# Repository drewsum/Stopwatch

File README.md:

# Stopwatch
Hardware stopwatch, no code or microcontroller. 

"Display Enable" pushbutton toggles the seven segment LED display on and off
"Count Reset" pushbutton resets the counted time back to 00:00:00
"Count Enable" pushbutton starts and stops the stopwatch

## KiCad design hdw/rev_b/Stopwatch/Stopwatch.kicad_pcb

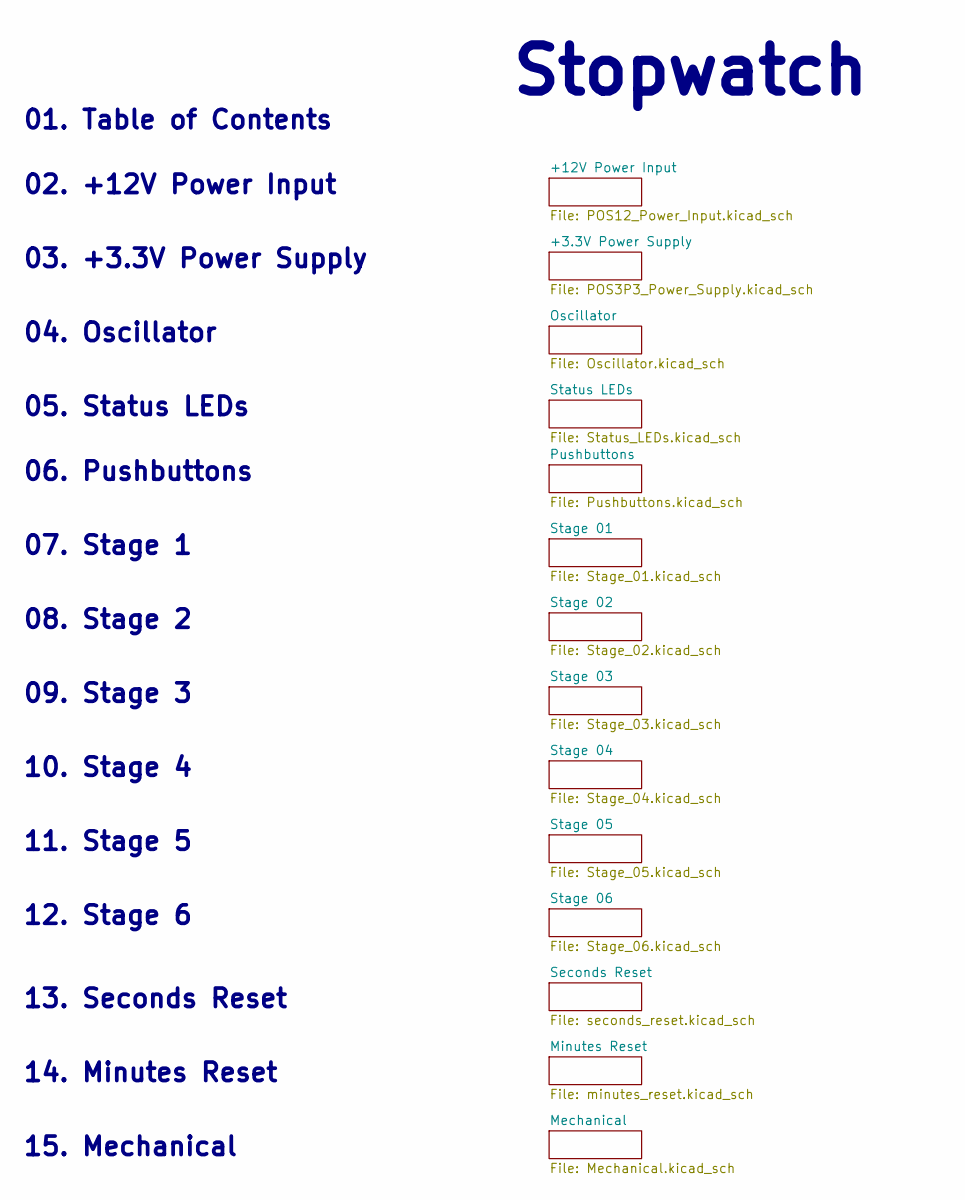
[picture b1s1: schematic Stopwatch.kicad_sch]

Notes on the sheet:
12. Stage 6
09. Stage 3
05. Status LEDs
10. Stage 4
15. Mechanical
Stopwatch
03. +3.3V Power Supply
01. Table of Contents
14. Minutes Reset
08. Stage 2
06. Pushbuttons
02. +12V Power Input
07. Stage 1
11. Stage 5
13. Seconds Reset
04. Oscillator

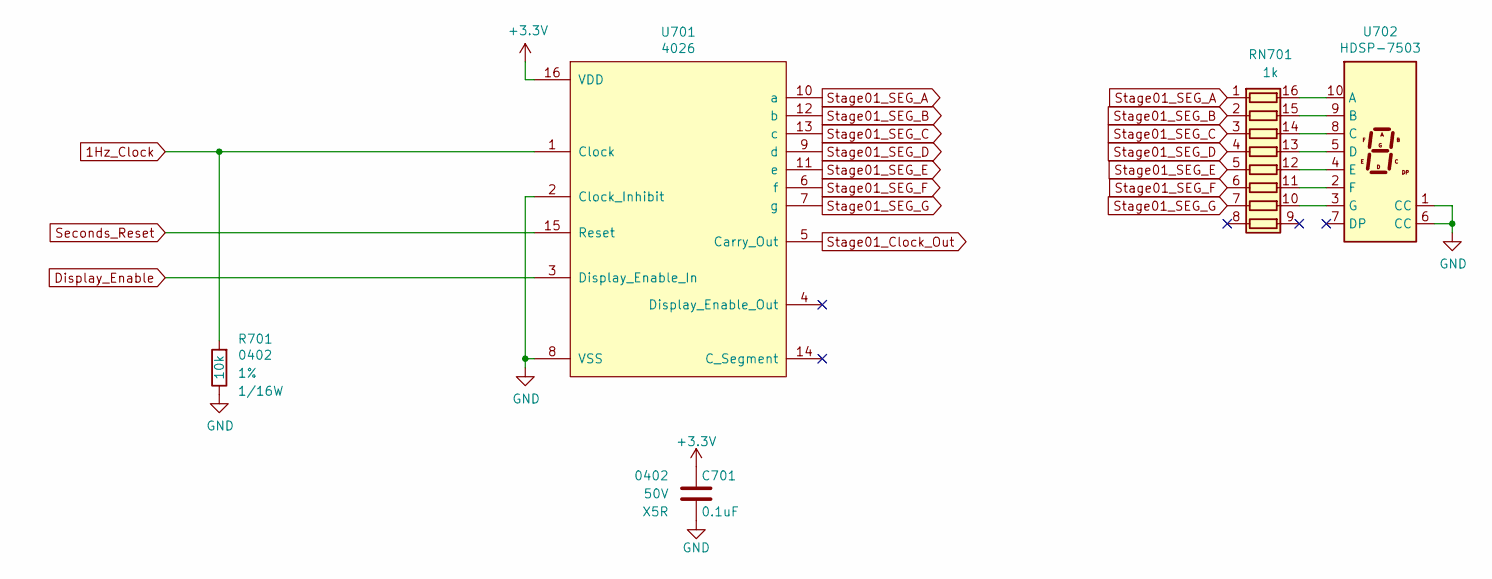
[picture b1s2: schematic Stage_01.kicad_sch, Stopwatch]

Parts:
C701: 0.1uF; C_0402; Voltage 50V; Digi-Key PN 490-10697-1-ND
R701: 10k; R_0402; Tolerance 1%; Digi-Key PN RMCF0402FT10K0CT-ND
RN701: 1k; R_Cat16-8; Digi-Key PN CAT16-102J8LFCT-ND
U701: 4026; TSSOP-16_4.4x5mm_Pitch0.65mm; Digi-Key PN 296-32878-5-ND
U702: HDSP-7503; HDSP-A151; Digi-Key PN 516-1203-5-ND

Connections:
1Hz_Clock: R701.1, U701.1 (Clock); also elsewhere on the board
+3.3V: C701.1, U701.16 (VDD); also elsewhere on the board
Display_Enable: U701.3 (Display_Enable_In); also elsewhere on the board
GND: C701.2, R701.2, U701.2 (Clock_Inhibit), U701.8 (VSS), U702.1 (CC), U702.6 (CC); also elsewhere on the board
unnamed: RN701.16 (R1.2), U702.10 (A)
unnamed: RN701.15 (R2.2), U702.9 (B)
unnamed: RN701.14 (R3.2), U702.8 (C)
unnamed: RN701.13 (R4.2), U702.5 (D)
unnamed: RN701.12 (R5.2), U702.4 (E)
unnamed: RN701.11 (R6.2), U702.2 (F)
unnamed: RN701.10 (R7.2), U702.3 (G)
Seconds_Reset: U701.15 (Reset); also elsewhere on the board
Stage01_Clock_Out: U701.5 (Carry_Out); also elsewhere on the board
Stage01_SEG_A: RN701.1 (R1.1), U701.10 (a)
Stage01_SEG_B: RN701.2 (R2.1), U701.12 (b)
Stage01_SEG_C: RN701.3 (R3.1), U701.13 (c)
Stage01_SEG_D: RN701.4 (R4.1), U701.9 (d)
Stage01_SEG_E: RN701.5 (R5.1), U701.11 (e)
Stage01_SEG_F: RN701.6 (R6.1), U701.6 (f)
Stage01_SEG_G: RN701.7 (R7.1), U701.7 (g)

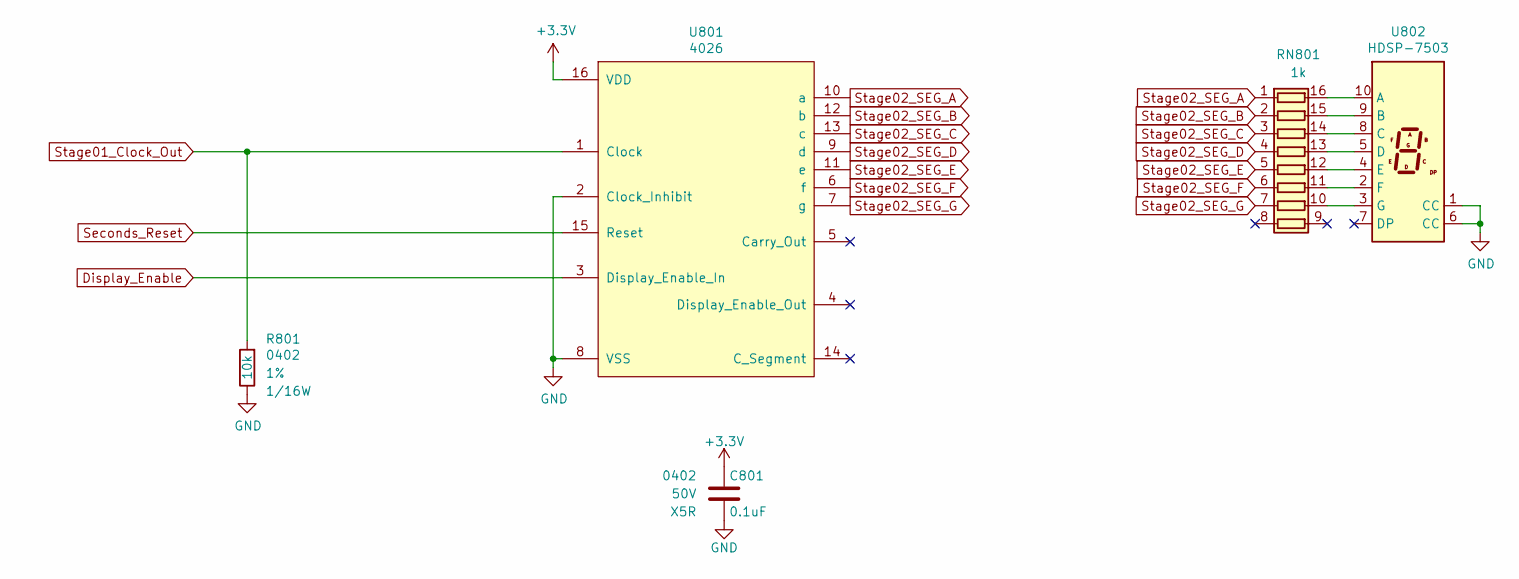
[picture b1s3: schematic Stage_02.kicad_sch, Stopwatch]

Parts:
C801: 0.1uF; C_0402; Voltage 50V; Digi-Key PN 490-10697-1-ND
R801: 10k; R_0402; Tolerance 1%; Digi-Key PN RMCF0402FT10K0CT-ND
RN801: 1k; R_Cat16-8; Digi-Key PN CAT16-102J8LFCT-ND
U801: 4026; TSSOP-16_4.4x5mm_Pitch0.65mm; Digi-Key PN 296-32878-5-ND
U802: HDSP-7503; HDSP-A151; Digi-Key PN 516-1203-5-ND

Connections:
+3.3V: C801.1, U801.16 (VDD); also elsewhere on the board
Display_Enable: U801.3 (Display_Enable_In); also elsewhere on the board
GND: C801.2, R801.2, U801.2 (Clock_Inhibit), U801.8 (VSS), U802.1 (CC), U802.6 (CC); also elsewhere on the board
unnamed: RN801.16 (R1.2), U802.10 (A)
unnamed: RN801.15 (R2.2), U802.9 (B)
unnamed: RN801.14 (R3.2), U802.8 (C)
unnamed: RN801.13 (R4.2), U802.5 (D)
unnamed: RN801.12 (R5.2), U802.4 (E)
unnamed: RN801.11 (R6.2), U802.2 (F)
unnamed: RN801.10 (R7.2), U802.3 (G)
Seconds_Reset: U801.15 (Reset); also elsewhere on the board
Stage01_Clock_Out: R801.1, U801.1 (Clock); also elsewhere on the board
Stage02_SEG_A: RN801.1 (R1.1), U801.10 (a); also elsewhere on the board
Stage02_SEG_B: RN801.2 (R2.1), U801.12 (b); also elsewhere on the board
Stage02_SEG_C: RN801.3 (R3.1), U801.13 (c); also elsewhere on the board
Stage02_SEG_D: RN801.4 (R4.1), U801.9 (d); also elsewhere on the board
Stage02_SEG_E: RN801.5 (R5.1), U801.11 (e); also elsewhere on the board
Stage02_SEG_F: RN801.6 (R6.1), U801.6 (f); also elsewhere on the board
Stage02_SEG_G: RN801.7 (R7.1), U801.7 (g); also elsewhere on the board

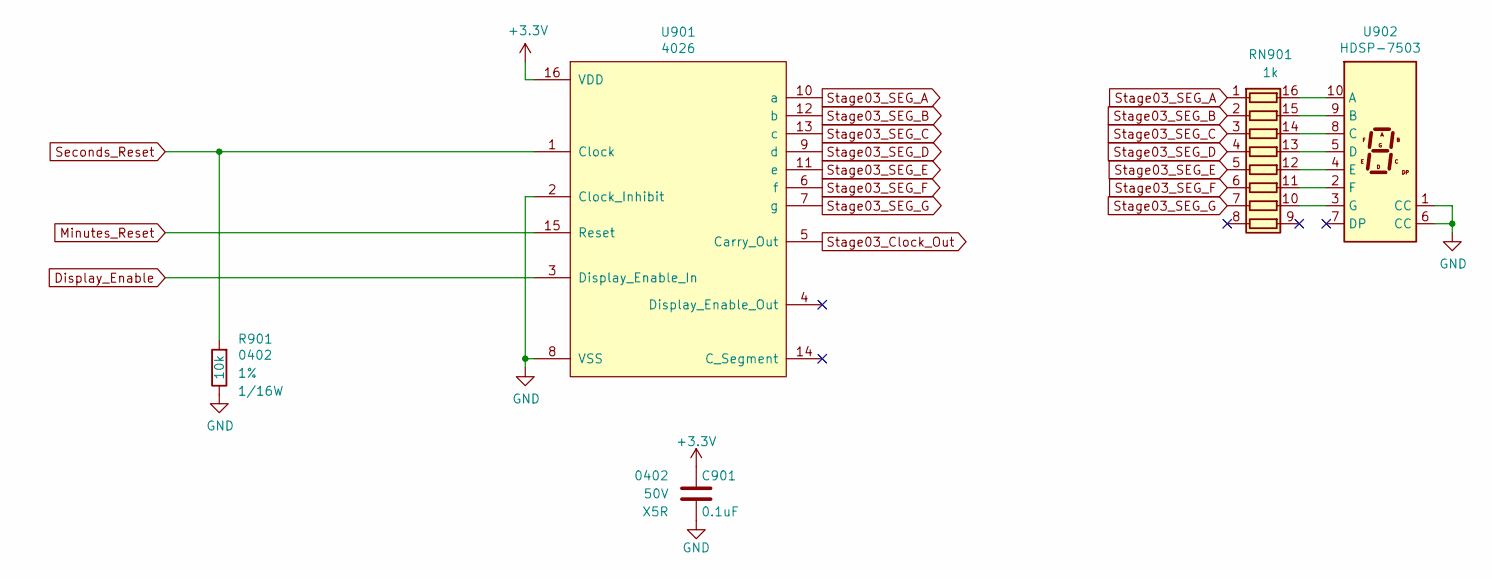
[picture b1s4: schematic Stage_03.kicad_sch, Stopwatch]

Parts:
C901: 0.1uF; C_0402; Voltage 50V; Digi-Key PN 490-10697-1-ND
R901: 10k; R_0402; Tolerance 1%; Digi-Key PN RMCF0402FT10K0CT-ND
RN901: 1k; R_Cat16-8; Digi-Key PN CAT16-102J8LFCT-ND
U901: 4026; TSSOP-16_4.4x5mm_Pitch0.65mm; Digi-Key PN 296-32878-5-ND
U902: HDSP-7503; HDSP-A151; Digi-Key PN 516-1203-5-ND

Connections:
+3.3V: C901.1, U901.16 (VDD); also elsewhere on the board
Display_Enable: U901.3 (Display_Enable_In); also elsewhere on the board
GND: C901.2, R901.2, U901.2 (Clock_Inhibit), U901.8 (VSS), U902.1 (CC), U902.6 (CC); also elsewhere on the board
Minutes_Reset: U901.15 (Reset); also elsewhere on the board
unnamed: RN901.16 (R1.2), U902.10 (A)
unnamed: RN901.15 (R2.2), U902.9 (B)
unnamed: RN901.14 (R3.2), U902.8 (C)
unnamed: RN901.13 (R4.2), U902.5 (D)
unnamed: RN901.12 (R5.2), U902.4 (E)
unnamed: RN901.11 (R6.2), U902.2 (F)
unnamed: RN901.10 (R7.2), U902.3 (G)
Seconds_Reset: R901.1, U901.1 (Clock); also elsewhere on the board
Stage03_Clock_Out: U901.5 (Carry_Out); also elsewhere on the board
Stage03_SEG_A: RN901.1 (R1.1), U901.10 (a)
Stage03_SEG_B: RN901.2 (R2.1), U901.12 (b)
Stage03_SEG_C: RN901.3 (R3.1), U901.13 (c)
Stage03_SEG_D: RN901.4 (R4.1), U901.9 (d)
Stage03_SEG_E: RN901.5 (R5.1), U901.11 (e)
Stage03_SEG_F: RN901.6 (R6.1), U901.6 (f)
Stage03_SEG_G: RN901.7 (R7.1), U901.7 (g)

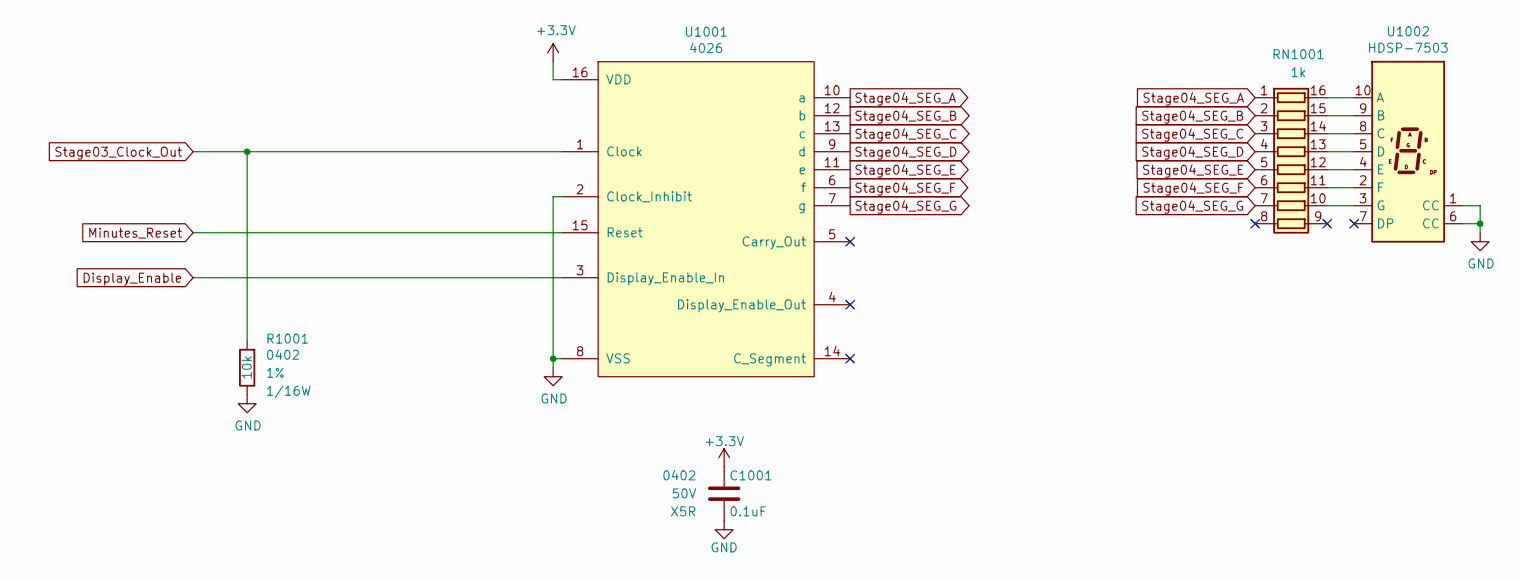
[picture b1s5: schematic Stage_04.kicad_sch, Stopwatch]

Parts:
C1001: 0.1uF; C_0402; Voltage 50V; Digi-Key PN 490-10697-1-ND
R1001: 10k; R_0402; Tolerance 1%; Digi-Key PN RMCF0402FT10K0CT-ND
RN1001: 1k; R_Cat16-8; Digi-Key PN CAT16-102J8LFCT-ND
U1001: 4026; TSSOP-16_4.4x5mm_Pitch0.65mm; Digi-Key PN 296-32878-5-ND
U1002: HDSP-7503; HDSP-A151; Digi-Key PN 516-1203-5-ND

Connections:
+3.3V: C1001.1, U1001.16 (VDD); also elsewhere on the board
Display_Enable: U1001.3 (Display_Enable_In); also elsewhere on the board
GND: C1001.2, R1001.2, U1001.2 (Clock_Inhibit), U1001.8 (VSS), U1002.1 (CC), U1002.6 (CC); also elsewhere on the board
Minutes_Reset: U1001.15 (Reset); also elsewhere on the board
unnamed: RN1001.16 (R1.2), U1002.10 (A)
unnamed: RN1001.15 (R2.2), U1002.9 (B)
unnamed: RN1001.14 (R3.2), U1002.8 (C)
unnamed: RN1001.13 (R4.2), U1002.5 (D)
unnamed: RN1001.12 (R5.2), U1002.4 (E)
unnamed: RN1001.11 (R6.2), U1002.2 (F)
unnamed: RN1001.10 (R7.2), U1002.3 (G)
Stage03_Clock_Out: R1001.1, U1001.1 (Clock); also elsewhere on the board
Stage04_SEG_A: RN1001.1 (R1.1), U1001.10 (a); also elsewhere on the board
Stage04_SEG_B: RN1001.2 (R2.1), U1001.12 (b); also elsewhere on the board
Stage04_SEG_C: RN1001.3 (R3.1), U1001.13 (c); also elsewhere on the board
Stage04_SEG_D: RN1001.4 (R4.1), U1001.9 (d); also elsewhere on the board
Stage04_SEG_E: RN1001.5 (R5.1), U1001.11 (e); also elsewhere on the board
Stage04_SEG_F: RN1001.6 (R6.1), U1001.6 (f); also elsewhere on the board
Stage04_SEG_G: RN1001.7 (R7.1), U1001.7 (g); also elsewhere on the board

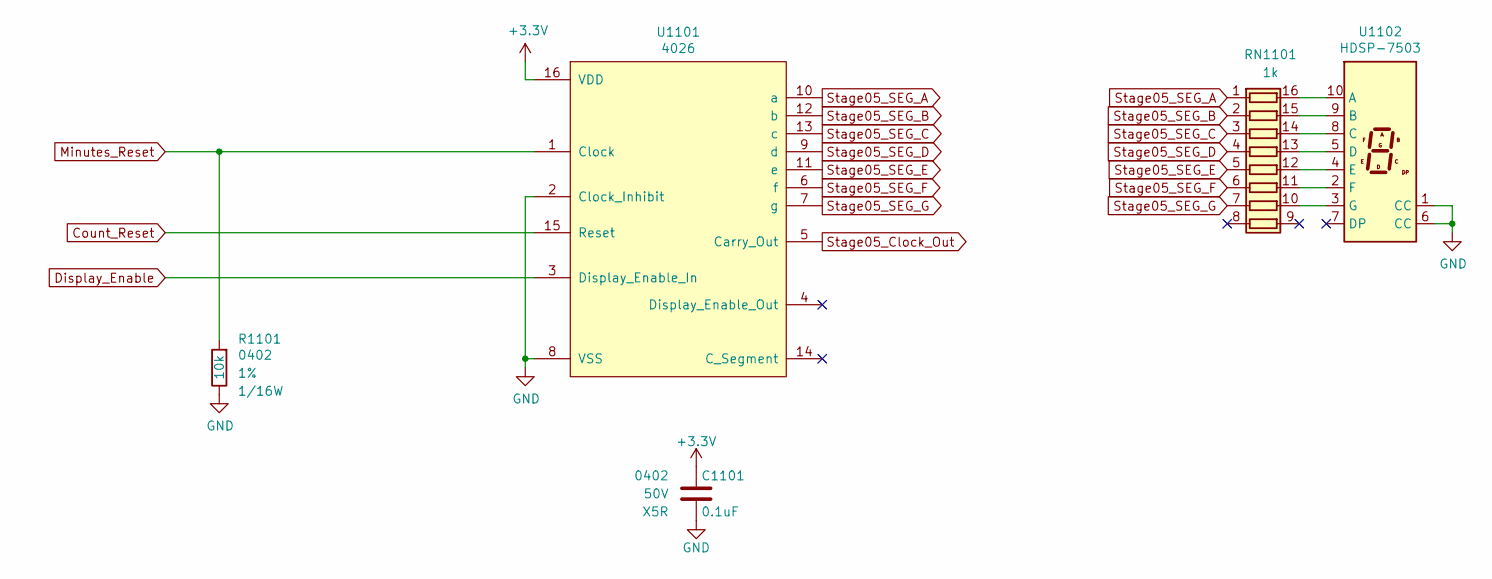
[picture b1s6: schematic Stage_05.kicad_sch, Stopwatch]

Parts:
C1101: 0.1uF; C_0402; Voltage 50V; Digi-Key PN 490-10697-1-ND
R1101: 10k; R_0402; Tolerance 1%; Digi-Key PN RMCF0402FT10K0CT-ND
RN1101: 1k; R_Cat16-8; Digi-Key PN CAT16-102J8LFCT-ND
U1101: 4026; TSSOP-16_4.4x5mm_Pitch0.65mm; Digi-Key PN 296-32878-5-ND
U1102: HDSP-7503; HDSP-A151; Digi-Key PN 516-1203-5-ND

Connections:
+3.3V: C1101.1, U1101.16 (VDD); also elsewhere on the board
Count_Reset: U1101.15 (Reset); also elsewhere on the board
Display_Enable: U1101.3 (Display_Enable_In); also elsewhere on the board
GND: C1101.2, R1101.2, U1101.2 (Clock_Inhibit), U1101.8 (VSS), U1102.1 (CC), U1102.6 (CC); also elsewhere on the board
Minutes_Reset: R1101.1, U1101.1 (Clock); also elsewhere on the board
unnamed: RN1101.16 (R1.2), U1102.10 (A)
unnamed: RN1101.15 (R2.2), U1102.9 (B)
unnamed: RN1101.14 (R3.2), U1102.8 (C)
unnamed: RN1101.13 (R4.2), U1102.5 (D)
unnamed: RN1101.12 (R5.2), U1102.4 (E)
unnamed: RN1101.11 (R6.2), U1102.2 (F)
unnamed: RN1101.10 (R7.2), U1102.3 (G)
Stage05_Clock_Out: U1101.5 (Carry_Out); also elsewhere on the board
Stage05_SEG_A: RN1101.1 (R1.1), U1101.10 (a)
Stage05_SEG_B: RN1101.2 (R2.1), U1101.12 (b)
Stage05_SEG_C: RN1101.3 (R3.1), U1101.13 (c)
Stage05_SEG_D: RN1101.4 (R4.1), U1101.9 (d)
Stage05_SEG_E: RN1101.5 (R5.1), U1101.11 (e)
Stage05_SEG_F: RN1101.6 (R6.1), U1101.6 (f)
Stage05_SEG_G: RN1101.7 (R7.1), U1101.7 (g)

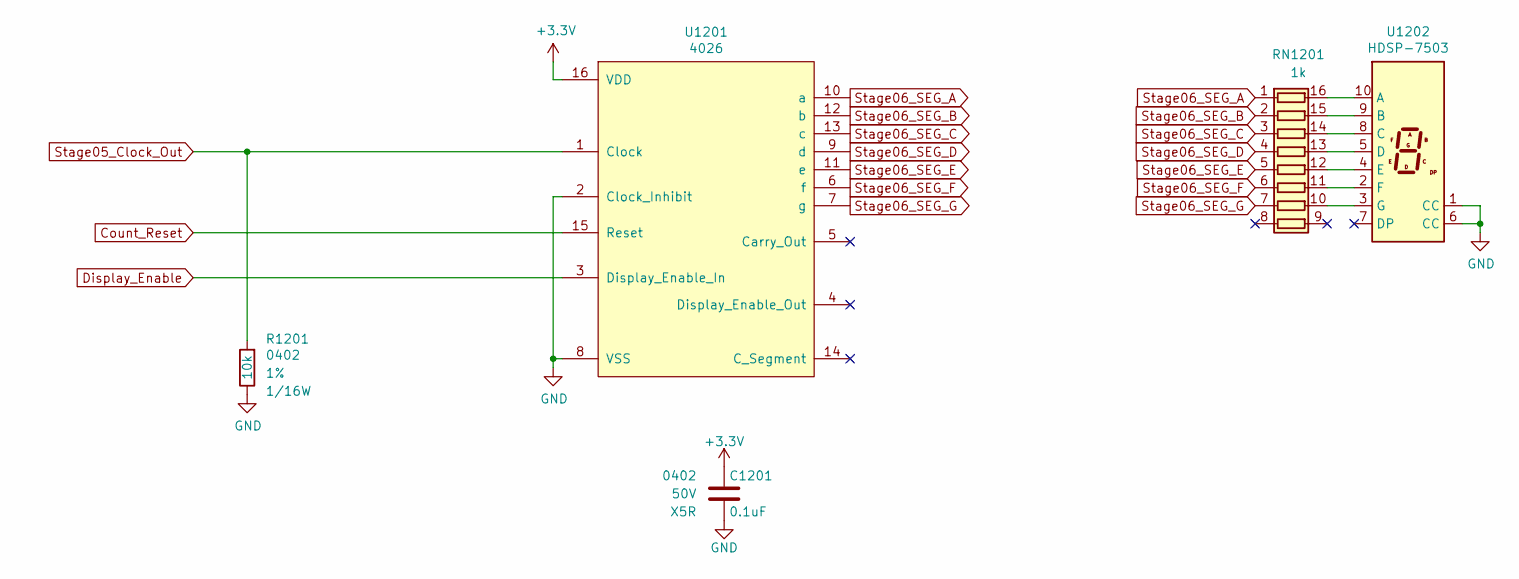
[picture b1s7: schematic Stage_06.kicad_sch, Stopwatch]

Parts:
C1201: 0.1uF; C_0402; Voltage 50V; Digi-Key PN 490-10697-1-ND
R1201: 10k; R_0402; Tolerance 1%; Digi-Key PN RMCF0402FT10K0CT-ND
RN1201: 1k; R_Cat16-8; Digi-Key PN CAT16-102J8LFCT-ND
U1201: 4026; TSSOP-16_4.4x5mm_Pitch0.65mm; Digi-Key PN 296-32878-5-ND
U1202: HDSP-7503; HDSP-A151; Digi-Key PN 516-1203-5-ND

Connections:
+3.3V: C1201.1, U1201.16 (VDD); also elsewhere on the board
Count_Reset: U1201.15 (Reset); also elsewhere on the board
Display_Enable: U1201.3 (Display_Enable_In); also elsewhere on the board
GND: C1201.2, R1201.2, U1201.2 (Clock_Inhibit), U1201.8 (VSS), U1202.1 (CC), U1202.6 (CC); also elsewhere on the board
unnamed: RN1201.16 (R1.2), U1202.10 (A)
unnamed: RN1201.15 (R2.2), U1202.9 (B)
unnamed: RN1201.14 (R3.2), U1202.8 (C)
unnamed: RN1201.13 (R4.2), U1202.5 (D)
unnamed: RN1201.12 (R5.2), U1202.4 (E)
unnamed: RN1201.11 (R6.2), U1202.2 (F)
unnamed: RN1201.10 (R7.2), U1202.3 (G)
Stage05_Clock_Out: R1201.1, U1201.1 (Clock); also elsewhere on the board
Stage06_SEG_A: RN1201.1 (R1.1), U1201.10 (a)
Stage06_SEG_B: RN1201.2 (R2.1), U1201.12 (b)
Stage06_SEG_C: RN1201.3 (R3.1), U1201.13 (c)
Stage06_SEG_D: RN1201.4 (R4.1), U1201.9 (d)
Stage06_SEG_E: RN1201.5 (R5.1), U1201.11 (e)
Stage06_SEG_F: RN1201.6 (R6.1), U1201.6 (f)
Stage06_SEG_G: RN1201.7 (R7.1), U1201.7 (g)

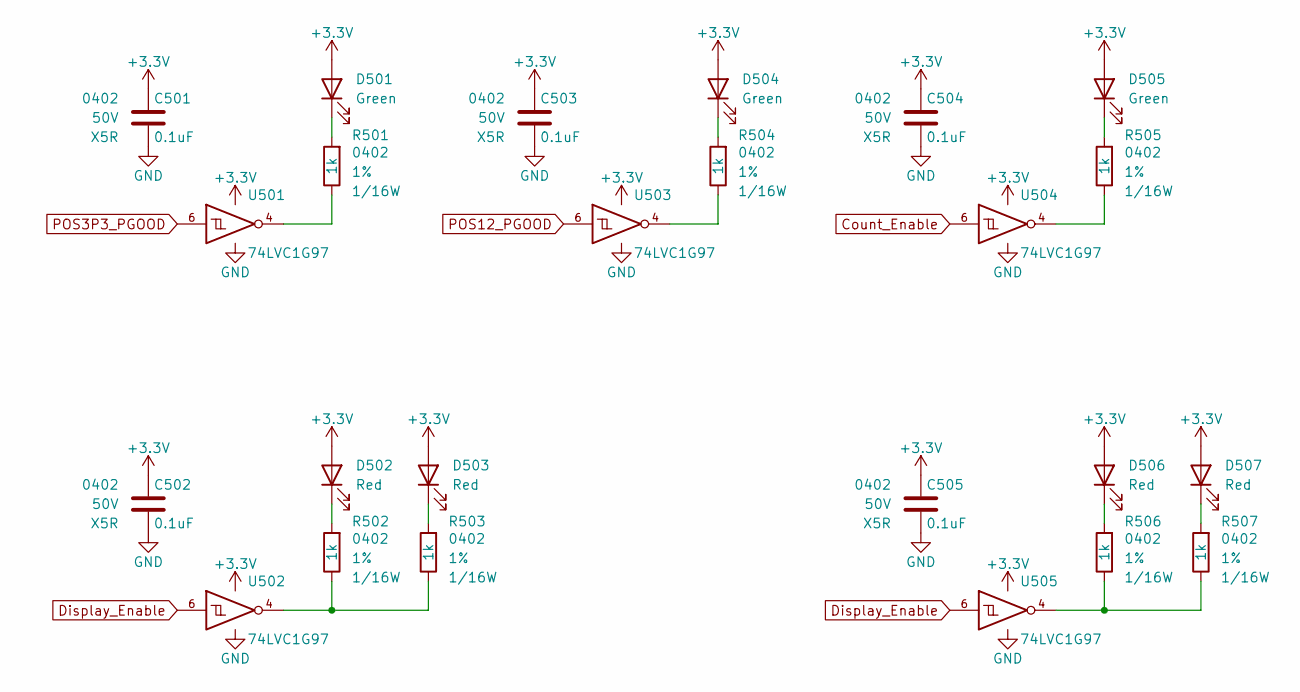
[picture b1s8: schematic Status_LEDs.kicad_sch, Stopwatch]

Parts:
C501, C502, C503, C504, C505: 0.1uF; C_0402; Voltage 50V; Digi-Key PN 490-10697-1-ND
D501, D504, D505: Green; LED_0402; Digi-Key PN 754-1101-1-ND
D502, D503, D506, D507: Red; LED_0402; Digi-Key PN 754-1104-1-ND
R501, R502, R503, R504, R505, R506, R507: 1k; R_0402; Tolerance 1%; Digi-Key PN RMCF0402FT1K00CT-ND
U501, U502, U503, U504, U505: 74LVC1G97; SOT-363_SC-70-6; Digi-Key PN 296-15582-1-ND

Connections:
+3.3V: C501.1, C502.1, C503.1, C504.1, C505.1, D501.2 (A), D502.2 (A), D503.2 (A), D504.2 (A), D505.2 (A), D506.2 (A), D507.2 (A), U501.1 (VCC), U501.5 (VCC), U502.1 (VCC), U502.5 (VCC), U503.1 (VCC), U503.5 (VCC), U504.1 (VCC), U504.5 (VCC), U505.1 (VCC), U505.5 (VCC); also elsewhere on the board
Count_Enable: U504.6; also elsewhere on the board
Display_Enable: U502.6, U505.6; also elsewhere on the board
GND: C501.2, C502.2, C503.2, C504.2, C505.2, U501.2 (GND), U501.3 (GND), U502.2 (GND), U502.3 (GND), U503.2 (GND), U503.3 (GND), U504.2 (GND), U504.3 (GND), U505.2 (GND), U505.3 (GND); also elsewhere on the board
unnamed: D501.1 (K), R501.1
unnamed: D502.1 (K), R502.1
unnamed: D503.1 (K), R503.1
unnamed: D504.1 (K), R504.1
unnamed: D505.1 (K), R505.1
unnamed: D506.1 (K), R506.1
unnamed: D507.1 (K), R507.1
unnamed: R501.2, U501.4
unnamed: R502.2, R503.2, U502.4
unnamed: R504.2, U503.4
unnamed: R505.2, U504.4
unnamed: R506.2, R507.2, U505.4
POS3P3_PGOOD: U501.6; also elsewhere on the board
POS12_PGOOD: U503.6; also elsewhere on the board

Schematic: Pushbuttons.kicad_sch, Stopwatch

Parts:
C601, C602, C603: 10nF; C_0402; Voltage 50V; Digi-Key PN 445-12201-1-ND
C604, C605, C606, C610, C611, C612, C613, C614: 0.1uF; C_0402; Voltage 50V; Digi-Key PN 490-10697-1-ND
C607, C608, C609: 10uF; C_0402; Voltage 10V; Digi-Key PN 490-GRM155R61A106ME11DCT-ND
R601, R602, R603, R604, R605, R606: 1k; R_0402; Tolerance 1%; Digi-Key PN RMCF0402FT1K00CT-ND
R607, R608, R609, R610, R611, R612, R613, R614, R615, R616, R617: 10k; R_0402; Tolerance 1%; Digi-Key PN RMCF0402FT10K0CT-ND
SW601, SW602, SW603: Cap_Touch; Capacitive_Touch_Pad
U601, U602, U603: AT42QT1010-TSHR; SOT-23-6; Digi-Key PN AT42QT1010-TSHRCT-ND
U604, U605, U606: 74LVC1G97; SOT-363_SC-70-6; Digi-Key PN 296-15582-1-ND
U607, U608: 74LVC1G80; SOT-353_SC-70-5; Digi-Key PN 296-41824-1-ND

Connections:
+3.3V: C604.1, C605.1, C606.1, C610.1, C611.1, C612.1, C613.1, C614.1, U601.5 (VDD), U601.6 (SYNC), U602.5 (VDD), U602.6 (SYNC), U603.5 (VDD), U603.6 (SYNC), U604.5 (VCC), U605.5 (VCC), U606.5 (VCC), U607.5 (VCC), U608.5 (VCC); also elsewhere on the board
Count_Enable: R617.1, U608.1 (D), U608.4 (~Q); also elsewhere on the board
Count_Reset: R613.1, U605.4; also elsewhere on the board
Display_Enable: R616.1, U607.1 (D), U607.4 (~Q); also elsewhere on the board
GND: C604.2, C605.2, C606.2, C607.2, C608.2, C609.2, C610.2, C611.2, C612.2, C613.2, C614.2, R607.2, R608.2, R609.2, R613.2, R614.2, R615.2, R616.2, R617.2, U601.2 (VSS), U602.2 (VSS), U603.2 (VSS), U604.2 (GND), U604.3 (GND), U604.6 (GND), U605.2 (GND), U605.3 (GND), U605.6 (GND), U606.2 (GND), U606.3 (GND), U606.6 (GND), U607.3 (GND), U608.3 (GND); also elsewhere on the board
unnamed: C607.1, R610.1, U604.1
unnamed: C608.1, R611.1, U605.1
unnamed: C609.1, R612.1, U606.1
unnamed: R601.1, R602.1, SW601.1 (TP)
unnamed: R603.1, R604.1, SW602.1 (TP)
unnamed: R605.1, R606.1, SW603.1 (TP)
unnamed: R607.1, R610.2, U601.1 (OUT)
unnamed: C601.1, U601.4 (SNS)
unnamed: C601.2, R601.2, R602.2, U601.3 (SNSK)
unnamed: R608.1, R611.2, U602.1 (OUT)
unnamed: C602.1, U602.4 (SNS)
unnamed: C602.2, R603.2, R604.2, U602.3 (SNSK)
unnamed: R609.1, R612.2, U603.1 (OUT)
unnamed: C603.1, U603.4 (SNS)
unnamed: C603.2, R605.2, R606.2, U603.3 (SNSK)
unnamed: R614.1, U604.4, U607.2 (C)
unnamed: R615.1, U606.4, U608.2 (C)

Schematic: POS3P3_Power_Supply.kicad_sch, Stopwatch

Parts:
C301, C305, C306: 10uF; C_1206; Voltage 25V; Digi-Key PN 1276-7031-1-ND
C302: 10uF; C_0402; Voltage 10V; Digi-Key PN 490-GRM155R61A106ME11DCT-ND
C303: 10nF; C_0402; Voltage 50V; Digi-Key PN 445-12201-1-ND
C304: 0.1uF; C_0402; Voltage 50V; Digi-Key PN 490-10697-1-ND
D301: BAT48JFILM; D_SOD-323; Digi-Key PN 497-5711-1-ND
L301: 2.2u; L_Vishay_IHLP-2020; Tolerance 20%; Digi-Key PN 541-1236-1-ND
Q301: BSS214NW; SOT-323_SC-70; Digi-Key PN BSS214NWH6327XTSA1CT-ND
Q302: ZXMS6004FFTA; SOT-23; Digi-Key PN ZXMS6004FFCT-ND
R301: 10; R_0402; Tolerance 1%; Digi-Key PN RMCF0402FT10R0CT-ND
R302, R303: 10k; R_0402; Tolerance 1%; Digi-Key PN RMCF0402FT10K0CT-ND
R304: 562k; R_0402; Tolerance 1%; Digi-Key PN RMCF0402FT562KCT-ND
R305: 180k; R_0402; Tolerance 1%; Digi-Key PN RMCF0402FT180KCT-ND
TP301: TP; Test_Point
U301: TPS62130A; QFN-16-1EP_3x3mm_Pitch0.5mm; Digi-Key PN 296-39446-1-ND

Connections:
+3.3V: C305.1, C306.1, D301.2 (A), L301.2, Q302.3 (D), R302.1, R304.1, TP301.1 (TP), U301.14 (VOS); also elsewhere on the board
+12V: C301.1, C304.1, U301.10 (AVIN), U301.11 (PVIN), U301.12 (PVIN); also elsewhere on the board
GND: C301.2, C302.2, C303.2, C304.2, C305.2, C306.2, Q301.2 (S), Q302.2 (S), R305.2, U301.6 (AGND), U301.7 (FSW), U301.8 (DEF), U301.15 (PGND), U301.16 (PGND), U301.17 (EP); also elsewhere on the board
unnamed: C302.1, D301.1 (K), R303.1
unnamed: L301.1, U301.1 (SW), U301.2 (SW), U301.3 (SW)
unnamed: Q301.3 (D), Q302.1 (G), R303.2
unnamed: R304.2, R305.1, U301.5 (FB)
unnamed: C303.1, U301.9 (SS/TR)
POS3P3_PGOOD: R302.2, U301.4 (PG); also elsewhere on the board
POS3P3_RUN: Q301.1 (G), R301.2, U301.13 (EN)
POS12_PGOOD: R301.1; also elsewhere on the board

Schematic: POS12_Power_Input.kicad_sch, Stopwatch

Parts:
C201: 10nF; C_0402; Voltage 50V; Digi-Key PN 445-12201-1-ND
C202: 0.1uF; C_0402; Voltage 50V; Digi-Key PN 490-10697-1-ND
C203: 100uF; CP_EIA-7343-43_Kemet-X; Voltage 16V; Tolerance 10%; Digi-Key PN 718-1102-1-ND
D201: 24V; D_SMA; Digi-Key PN SMAJ24CALFCT-ND; not fitted
J201: +12V IN; BARREL_JACK; Digi-Key PN CP-202BH-ND
N201: +12V 1A Power Supply; Digi-Key PN 993-1335-ND
R201: 51.1k; R_0402; Tolerance 1%; Digi-Key PN RMCF0402FT51K1CT-ND
R202: 1.15k; R_0402; Tolerance 1%; Digi-Key PN RMCF0402FT1K15CT-ND
R203, R207: 5.11k; R_0402; Tolerance 1%; Digi-Key PN RMCF0402FT5K11CT-ND
R204, R205, R208: 10k; R_0402; Tolerance 1%; Digi-Key PN RMCF0402FT10K0CT-ND
R206: 13k; R_0402; Tolerance 1%; Digi-Key PN RMCF0402FT13K0CT-ND
TP201: TP; PinHeader_1x01_P2.54mm_Horizontal
TP202, TP203: TP_Pad; Test_Point
U201: TPS26600RHFT; QFN-24-1EP_4x5mm_Pitch0.5mm; Digi-Key PN 296-45478-1-ND

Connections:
+12V: C203.1, R206.1, TP203.1 (TP), U201.23 (OUT), U201.24 (OUT); also elsewhere on the board
+12Vin: C202.1, D201.1 (A1), J201.1, R201.1, R204.1, TP202.1 (TP), U201.8 (IN), U201.9 (IN)
GND: C202.2, C203.2, D201.2 (A2), J201.2, J201.3, R207.2, TP201.1 (TP), U201.17 (GND); also elsewhere on the board
unnamed: R205.1, U201.19 (ILIM)
unnamed: R208.1, U201.18 (IMON)
unnamed: R202.2, R203.1, U201.12 (OVP)
unnamed: C201.2, R203.2, R205.2, R208.2, U201.15 (RTN), U201.25 (RTN_PAD)
unnamed: R201.2, R202.1, U201.10 (UVLO)
unnamed: C201.1, U201.20 (dVdT)
unnamed: R204.2, U201.14 (~SHDN)
POS12_PGOOD: R206.2, R207.1, U201.22 (~FLT); also elsewhere on the board

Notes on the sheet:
+3.3V Logic Level
UVLO threshold set to 10.8V OVLO threshold set to 13.2V MODE set to Circuit Breaker with Auto-Retry

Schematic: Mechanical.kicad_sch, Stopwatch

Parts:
H1501, H1502, H1503, H1504: 3mm; MountingHole_3mm

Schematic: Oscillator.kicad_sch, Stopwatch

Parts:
C401, C404, C405, C406: 0.1uF; C_0402; Voltage 50V; Digi-Key PN 490-10697-1-ND
C402: 10nF; C_0402; Voltage 50V; Digi-Key PN 445-12201-1-ND
C403: 1nF; C_0402; Voltage 50V; Digi-Key PN 445-7376-1-ND
R401, R402, R403, R404, R405, R406: 10k; R_0402; Tolerance 1%; Digi-Key PN RMCF0402FT10K0CT-ND
U401: 74LVC1G97; SOT-363_SC-70-6; Digi-Key PN 296-15582-1-ND
U402: CD4024; TSSOP-14_4.4x5mm_Pitch0.65mm; Digi-Key PN 296-49578-ND
U403: CD4040; DHVQFN16-1ep_3p5x2p5mm; Digi-Key PN 1727-7992-1-ND
X401: ECS-327KE; Oscillator_SMD_Abracon_ASE-4Pin_3.2x2.5mm; Digi-Key PN XC1751CT-ND

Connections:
1Hz_Clock: R404.1, U401.4; also elsewhere on the board
1Hz_Clock_SRC: R402.1, U401.3, U403.13 (Q7)
256Hz_Clock: R405.1, U402.3 (Q6), U403.10 (CLK)
32768Hz_Clock: R401.1, U402.1 (~CP), X401.3 (OUT)
+3.3V: C401.1, C402.1, C403.1, C404.1, C405.1, C406.1, U401.5 (VCC), U402.14 (VCC), U403.16 (VDD), X401.4 (Vdd); also elsewhere on the board
Count_Enable: U401.6; also elsewhere on the board
Count_Reset: R403.1, R406.1, U402.2 (MR), U403.11 (Reset); also elsewhere on the board
GND: C401.2, C402.2, C403.2, C404.2, C405.2, C406.2, R401.2, R402.2, R403.2, R404.2, R405.2, R406.2, U401.1 (GND), U401.2 (GND), U402.7 (GND), U403.8 (VSS), X401.2 (GND); also elsewhere on the board
POS3P3_PGOOD: X401.1 (EN); also elsewhere on the board

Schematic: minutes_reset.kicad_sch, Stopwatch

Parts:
C1401, C1402, C1403, C1404, C1405, C1406, C1407: 0.1uF; C_0402; Voltage 50V; Digi-Key PN 490-10697-1-ND
R1401, R1402, R1403, R1404, R1405, R1406, R1407: 10k; R_0402; Tolerance 1%; Digi-Key PN RMCF0402FT10K0CT-ND
U1401, U1402, U1403, U1404, U1405, U1406, U1407: 74LVC1G97; SOT-363_SC-70-6; Digi-Key PN 296-15582-1-ND

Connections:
+3.3V: C1401.1, C1402.1, C1403.1, C1404.1, C1405.1, C1406.1, C1407.1, U1401.5 (VCC), U1402.5 (VCC), U1403.5 (VCC), U1404.5 (VCC), U1405.5 (VCC), U1406.5 (VCC), U1407.3 (VCC), U1407.5 (VCC); also elsewhere on the board
Count_Reset: U1407.1; also elsewhere on the board
GND: C1401.2, C1402.2, C1403.2, C1404.2, C1405.2, C1406.2, C1407.2, R1401.2, R1402.2, R1403.2, R1404.2, R1405.2, R1406.2, R1407.2, U1401.2 (GND), U1401.3 (GND), U1402.1 (GND), U1402.2 (GND), U1403.1 (GND), U1403.2 (GND), U1404.1 (GND), U1404.2 (GND), U1405.1 (GND), U1405.2 (GND), U1406.1 (GND), U1406.2 (GND), U1407.2 (GND); also elsewhere on the board
Minutes_Reset: R1407.1, U1407.4; also elsewhere on the board
unnamed: R1401.1, U1401.4, U1404.6
unnamed: R1402.1, U1402.4, U1404.3
unnamed: R1403.1, U1403.4, U1405.6
unnamed: R1404.1, U1404.4, U1406.6
unnamed: R1405.1, U1405.4, U1406.3
unnamed: R1406.1, U1406.4, U1407.6
Stage04_SEG_A: U1402.3; also elsewhere on the board
Stage04_SEG_B: U1401.6; also elsewhere on the board
Stage04_SEG_C: U1402.6; also elsewhere on the board
Stage04_SEG_D: U1401.1; also elsewhere on the board
Stage04_SEG_E: U1403.6; also elsewhere on the board
Stage04_SEG_F: U1403.3; also elsewhere on the board
Stage04_SEG_G: U1405.3; also elsewhere on the board

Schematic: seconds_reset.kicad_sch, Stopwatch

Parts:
C1301, C1302, C1303, C1304, C1305, C1306, C1307: 0.1uF; C_0402; Voltage 50V; Digi-Key PN 490-10697-1-ND
R1301, R1302, R1303, R1304, R1305, R1306, R1307: 10k; R_0402; Tolerance 1%; Digi-Key PN RMCF0402FT10K0CT-ND
U1301, U1302, U1303, U1304, U1305, U1306, U1307: 74LVC1G97; SOT-363_SC-70-6; Digi-Key PN 296-15582-1-ND

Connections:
+3.3V: C1301.1, C1302.1, C1303.1, C1304.1, C1305.1, C1306.1, C1307.1, U1301.5 (VCC), U1302.5 (VCC), U1303.5 (VCC), U1304.5 (VCC), U1305.5 (VCC), U1306.5 (VCC), U1307.3 (VCC), U1307.5 (VCC); also elsewhere on the board
Count_Reset: U1307.1; also elsewhere on the board
GND: C1301.2, C1302.2, C1303.2, C1304.2, C1305.2, C1306.2, C1307.2, R1301.2, R1302.2, R1303.2, R1304.2, R1305.2, R1306.2, R1307.2, U1301.2 (GND), U1301.3 (GND), U1302.1 (GND), U1302.2 (GND), U1303.1 (GND), U1303.2 (GND), U1304.1 (GND), U1304.2 (GND), U1305.1 (GND), U1305.2 (GND), U1306.1 (GND), U1306.2 (GND), U1307.2 (GND); also elsewhere on the board
unnamed: R1301.1, U1301.4, U1304.6
unnamed: R1302.1, U1302.4, U1304.3
unnamed: R1303.1, U1303.4, U1305.6
unnamed: R1304.1, U1304.4, U1306.6
unnamed: R1305.1, U1305.4, U1306.3
unnamed: R1306.1, U1306.4, U1307.6
Seconds_Reset: R1307.1, U1307.4; also elsewhere on the board
Stage02_SEG_A: U1302.3; also elsewhere on the board
Stage02_SEG_B: U1301.6; also elsewhere on the board
Stage02_SEG_C: U1302.6; also elsewhere on the board
Stage02_SEG_D: U1301.1; also elsewhere on the board
Stage02_SEG_E: U1303.6; also elsewhere on the board
Stage02_SEG_F: U1303.3; also elsewhere on the board
Stage02_SEG_G: U1305.3; also elsewhere on the board
